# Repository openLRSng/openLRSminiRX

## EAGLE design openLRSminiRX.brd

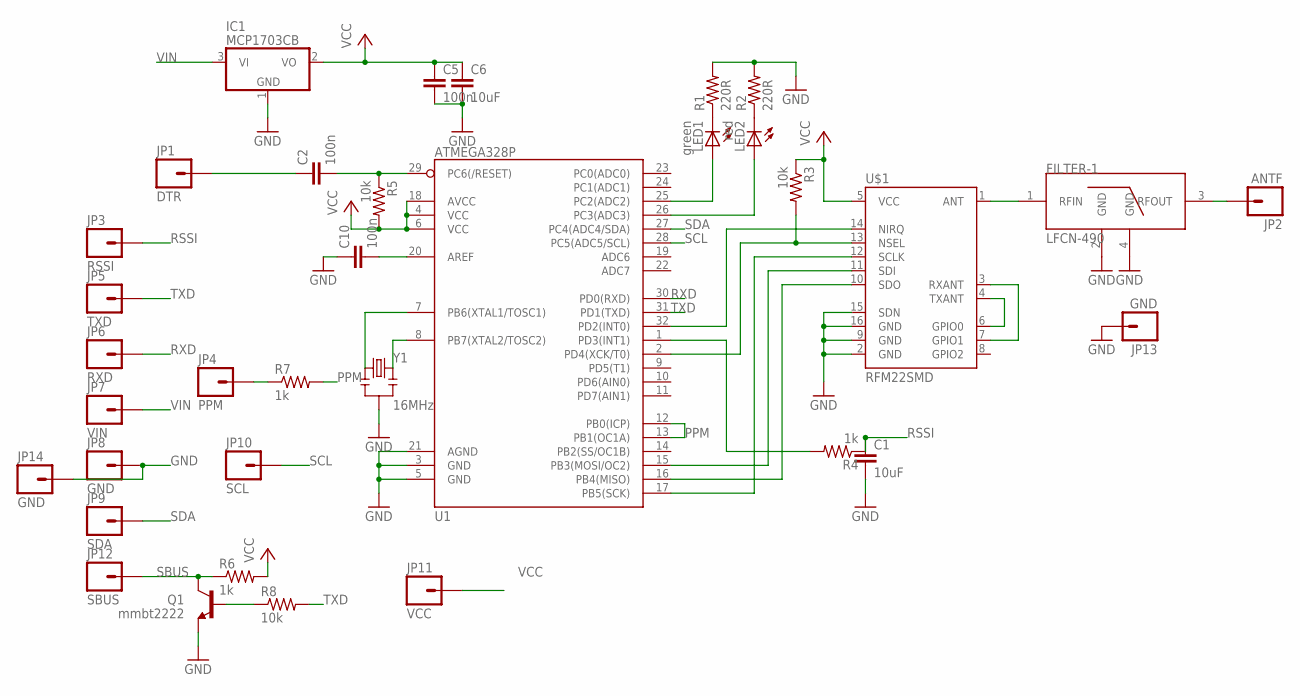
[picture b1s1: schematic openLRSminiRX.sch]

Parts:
C1, C6: 10uF; 0805
C2, C5, C10: 100n; 0805
FILTER-1: LFCN-490; FV1206
IC1: MCP1703CB; SOT23
JP1: DTR; 1X01
JP2: ANTF; 1X01
JP3: RSSI; 1X01
JP4: PPM; 1X01
JP5: TXD; 1X01
JP6: RXD; 1X01
JP7: VIN; 1X01
JP8, JP13, JP14: GND; 1X01
JP9: SDA; 1X01
JP10: SCL; 1X01
JP11: VCC; 1X01
JP12: SBUS; 1X01
LED1: green; SML0805
LED2: red; SML0805
Q1: mmbt2222; SOT23
R1, R2: 220R; 0805
R3, R5, R8: 10k; 0805
R4, R6, R7: 1k; 0805
U1: ATMEGA328P; TQFP32-08
U$1: RFM22SMD; RFM22-XXX-S2
Y1: 16MHz; RESONATOR-SMD

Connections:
GND: C1.2, C5.2, C6.2, C10.1, FILTER-1.2 (GND), FILTER-1.4 (GND), IC1.1 (GND), JP8.1, JP13.1, JP14.1, Q1.2 (E), R1.2, R2.2, U1.3 (GND), U1.5 (GND), U1.21 (AGND), U$1.2 (GND), U$1.9 (GND), U$1.15 (SDN), U$1.16 (GND), Y1.2
unnamed: FILTER-1.1 (RFIN), U$1.1 (ANT)
unnamed: U$1.4 (TXANT), U$1.6 (GPIO0)
unnamed: U$1.3 (RXANT), U$1.7 (GPIO1)
unnamed: FILTER-1.3 (RFOUT), JP2.1
unnamed: JP4.1, R7.1
unnamed: R4.2, U1.1 (PD3(INT1))
unnamed: U1.15 (PB3(MOSI/OC2)), U$1.11 (SDI)
unnamed: U1.16 (PB4(MISO)), U$1.10 (SDO)
unnamed: U1.17 (PB5(SCK)), U$1.12 (SCLK)
unnamed: R3.2, U1.2 (PD4(XCK/T0)), U$1.13 (NSEL)
unnamed: U1.32 (PD2(INT0)), U$1.14 (NIRQ)
unnamed: LED1.C, R1.1
unnamed: LED2.C, R2.1
unnamed: LED1.A, U1.25 (PC2(ADC2))
unnamed: LED2.A, U1.26 (PC3(ADC3))
unnamed: U1.7 (PB6(XTAL1/TOSC1)), Y1.1
unnamed: U1.8 (PB7(XTAL2/TOSC2)), Y1.3
unnamed: C2.2, R5.1, U1.29 (PC6(/RESET))
unnamed: C10.2, U1.20 (AREF)
unnamed: C2.1, JP1.1
unnamed: Q1.1 (B), R8.1
PPM: R7.2, U1.12 (PB0(ICP)), U1.13 (PB1(OC1A))
RSSI: C1.1, JP3.1, R4.1
RXD: JP6.1, U1.30 (PD0(RXD))
SBUS: JP12.1, Q1.3 (C), R6.1
SCL: JP10.1, U1.28 (PC5(ADC5/SCL))
SDA: JP9.1, U1.27 (PC4(ADC4/SDA))
TXD: JP5.1, R8.2, U1.31 (PD1(TXD))
VCC: C5.1, C6.1, IC1.2 (VO), JP11.1, R3.1, R5.2, R6.2, U1.4 (VCC), U1.6 (VCC), U1.18 (AVCC), U$1.5 (VCC)
VIN: IC1.3 (VI), JP7.1

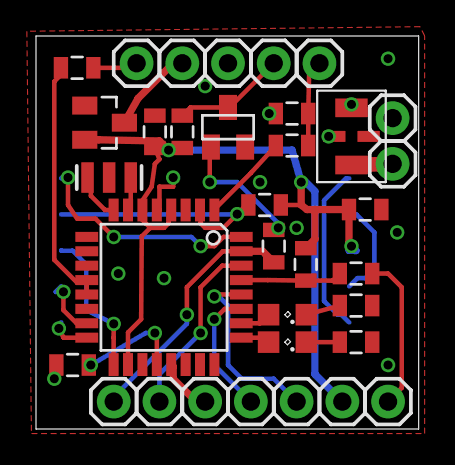
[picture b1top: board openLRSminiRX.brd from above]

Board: 2 copper layers, 21.3 x 21.8 mm, 35 parts (1 on the bottom side), 31 nets.

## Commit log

2014-01-24 Initial version
2014-01-24 update, fully routed.
2014-01-24 updates (fix RSSI output pin)
2014-01-24 cleanups
2014-01-24 Connect ICP to PPM (allow TX operation like on 6ch)
2014-01-25 add resonator (optional)
2014-02-06 Make filtter 'mandatory'. It is still possible to use without filter by soldering to pad directly.
2014-08-27 Fix SBUS inverter (add resistor between TXD and NPN B) Add DTR breakout (easier serial flashing)
2014-09-13 add 6pin arduino header, add sma, change board size, add diptrace files
2015-03-04 Add component values

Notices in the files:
parts and their libraries:
SparkFun-RF: Licensing: CC v3.0 Share-Alike You are welcome to use this library for commercial purposes.
